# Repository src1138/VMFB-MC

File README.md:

# VMFB-MC
Simplified version of the VMFB (https://github.com/src1138/VMFB) PCB designed with a smaller footprint and BOM to rely on a microcontroller or single-board computer to control and monitor it.

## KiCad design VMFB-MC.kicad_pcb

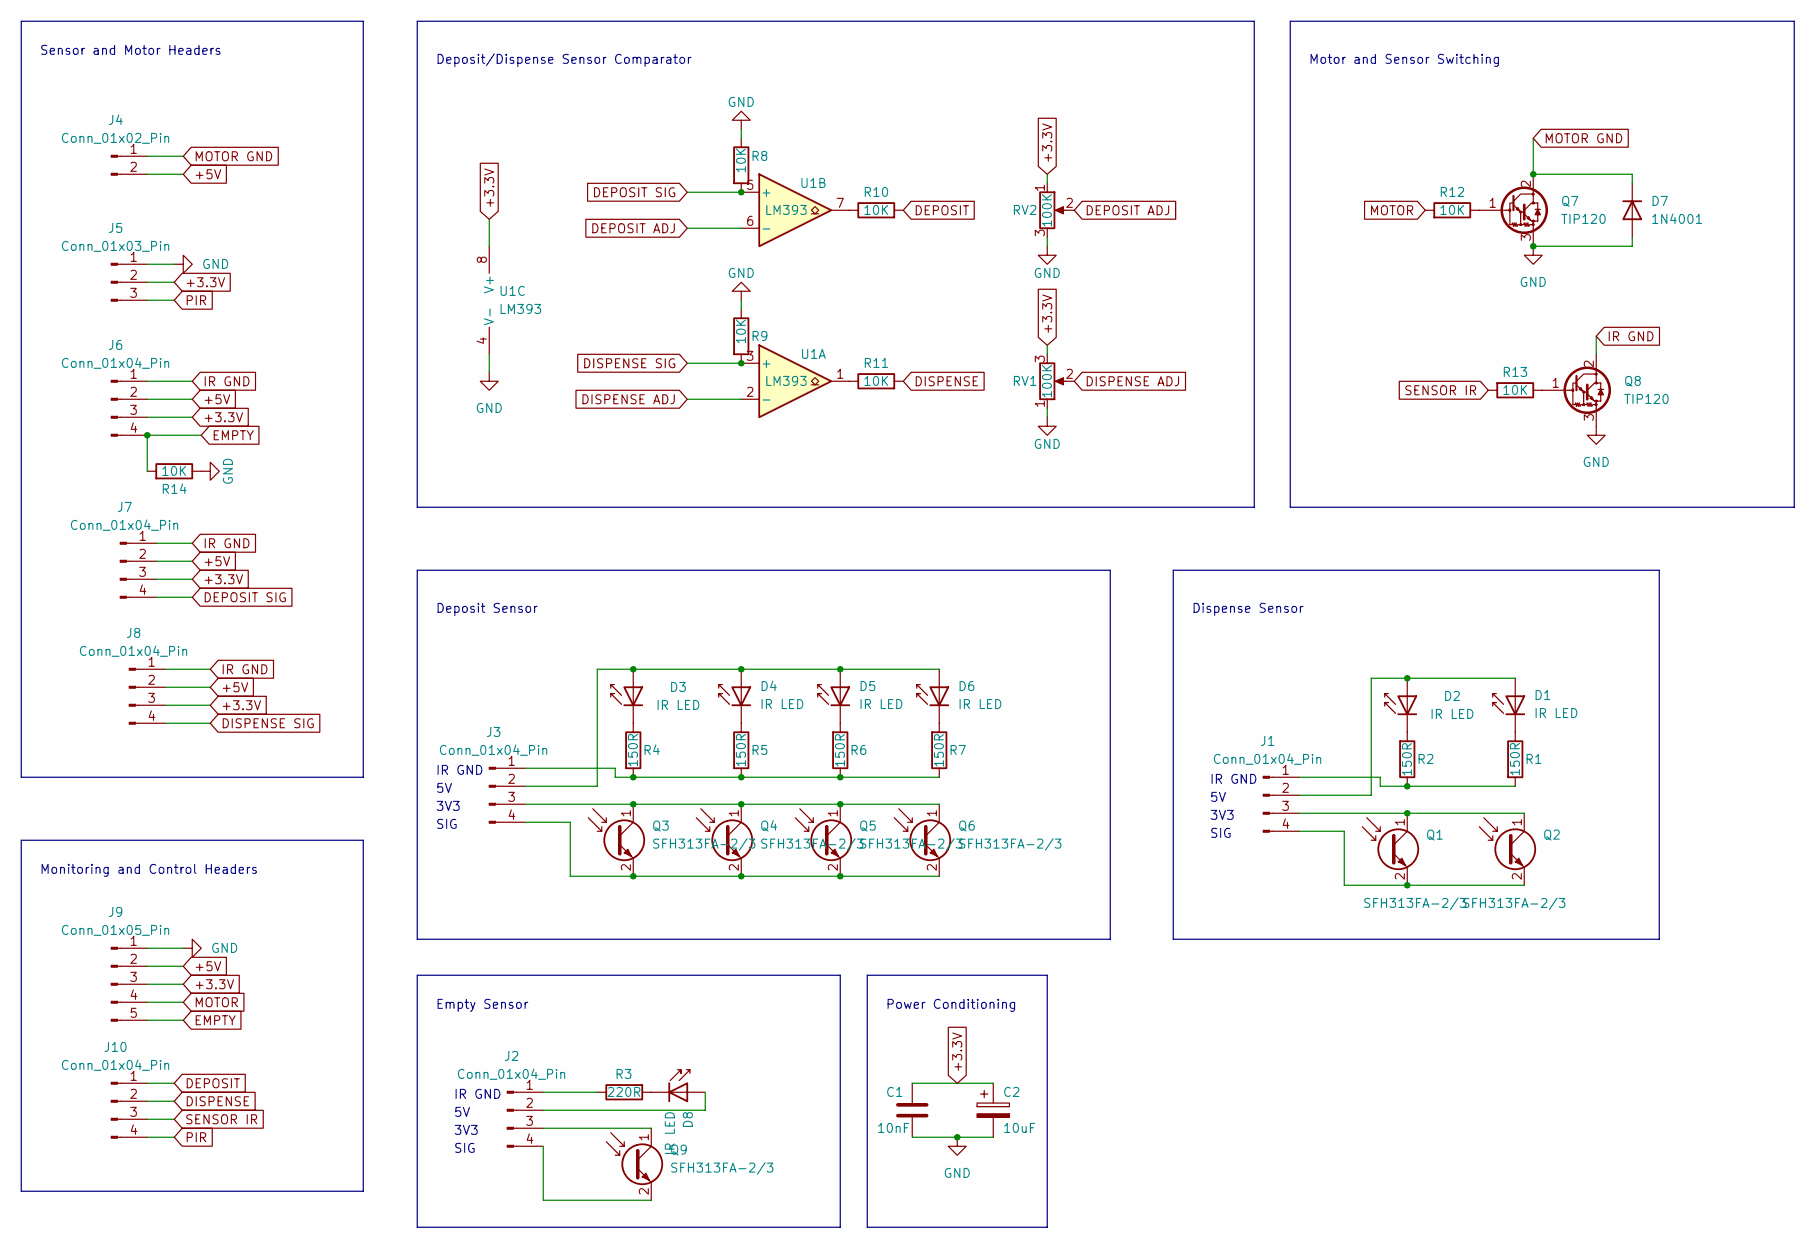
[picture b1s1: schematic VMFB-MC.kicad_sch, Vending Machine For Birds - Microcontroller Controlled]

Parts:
C1: 10nF; C_Disc_D5.0mm_W2.5mm_P2.50mm
C2: 10uF; CP_Radial_D5.0mm_P2.00mm
D1, D2, D3, D4, D5, D6, D8: IR LED; LED_D5.0mm_IRGrey
D7: 1N4001; D_DO-41_SOD81_P2.54mm_Vertical_KathodeUp
J1, J2, J3, J6, J7, J8, J10: Conn_01x04_Pin; PinHeader_1x04_P2.54mm_Vertical
J4: Conn_01x02_Pin; PinHeader_1x02_P2.54mm_Vertical
J5: Conn_01x03_Pin; PinHeader_1x03_P2.54mm_Vertical
J9: Conn_01x05_Pin; PinHeader_1x05_P2.54mm_Vertical
Q1, Q2, Q3, Q4, Q5, Q6, Q9: SFH313FA-2/3; LED_D5.0mm_IRBlack
Q7, Q8: TIP120; TO-220-3_Vertical
R1, R2, R4, R5, R6, R7: 150R; R_Axial_DIN0207_L6.3mm_D2.5mm_P2.54mm_Vertical
R3: 220R; R_Axial_DIN0207_L6.3mm_D2.5mm_P2.54mm_Vertical
R8, R9, R10, R11, R12, R13, R14: 10K; R_Axial_DIN0207_L6.3mm_D2.5mm_P2.54mm_Vertical
RV1, RV2: 100K; Potentiometer_Piher_PT-10-V10_Vertical
U1: LM393; DIP-8_W7.62mm

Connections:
+3.3V: C1.1, C2.1, J5.2, J6.3, J7.3, J8.3, J9.3, RV1.3, RV2.1, U1.8 (V+)
+5V: J4.2, J6.2, J7.2, J8.2, J9.2
DEPOSIT: J10.1, R10.2
DEPOSIT ADJ: RV2.2, U1.6 (-)
DEPOSIT SIG: J7.4, R8.2, U1.5 (+)
DISPENSE: J10.2, R11.2
DISPENSE ADJ: RV1.2, U1.2 (-)
DISPENSE SIG: J8.4, R9.2, U1.3 (+)
EMPTY: J6.4, J9.5, R14.2
GND: C1.2, C2.2, D7.2 (A), J5.1, J9.1, Q7.3 (E), Q8.3 (E), R8.1, R9.1, R14.1, RV1.1, RV2.3, U1.4 (V-)
IR GND: J6.1, J7.1, J8.1, Q8.2 (C)
MOTOR: J9.4, R12.2
MOTOR GND: D7.1 (K), J4.1, Q7.2 (C)
unnamed: D1.2 (A), D2.2 (A), J1.2
unnamed: D1.1 (K), R1.1
unnamed: D2.1 (K), R2.2
unnamed: D3.2 (A), D4.2 (A), D5.2 (A), D6.2 (A), J3.2
unnamed: D3.1 (K), R4.1
unnamed: D4.1 (K), R5.1
unnamed: D5.1 (K), R6.2
unnamed: D6.1 (K), R7.2
unnamed: D8.2 (A), J2.2
unnamed: D8.1 (K), R3.2
unnamed: J1.1, R1.2, R2.1
unnamed: J1.3, Q1.1 (C), Q2.1 (C)
unnamed: J1.4, Q1.2 (E), Q2.2 (E)
unnamed: J2.1, R3.1
unnamed: J2.3, Q9.1 (C)
unnamed: J2.4, Q9.2 (E)
unnamed: J3.1, R4.2, R5.2, R6.1, R7.1
unnamed: J3.3, Q3.1 (C), Q4.1 (C), Q5.1 (C), Q6.1 (C)
unnamed: J3.4, Q3.2 (E), Q4.2 (E), Q5.2 (E), Q6.2 (E)
unnamed: Q7.1 (B), R12.1
unnamed: Q8.1 (B), R13.1
unnamed: R10.1, U1.7
unnamed: R11.1, U1.1
PIR: J5.3, J10.4
SENSOR IR: J10.3, R13.2

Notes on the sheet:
Sensor and Motor Headers
IR GND
Monitoring and Control Headers
3V3
Motor and Sensor Switching
SIG
Deposit Sensor
Dispense Sensor
Empty Sensor
Power Conditioning
Deposit/Dispense Sensor Comparator

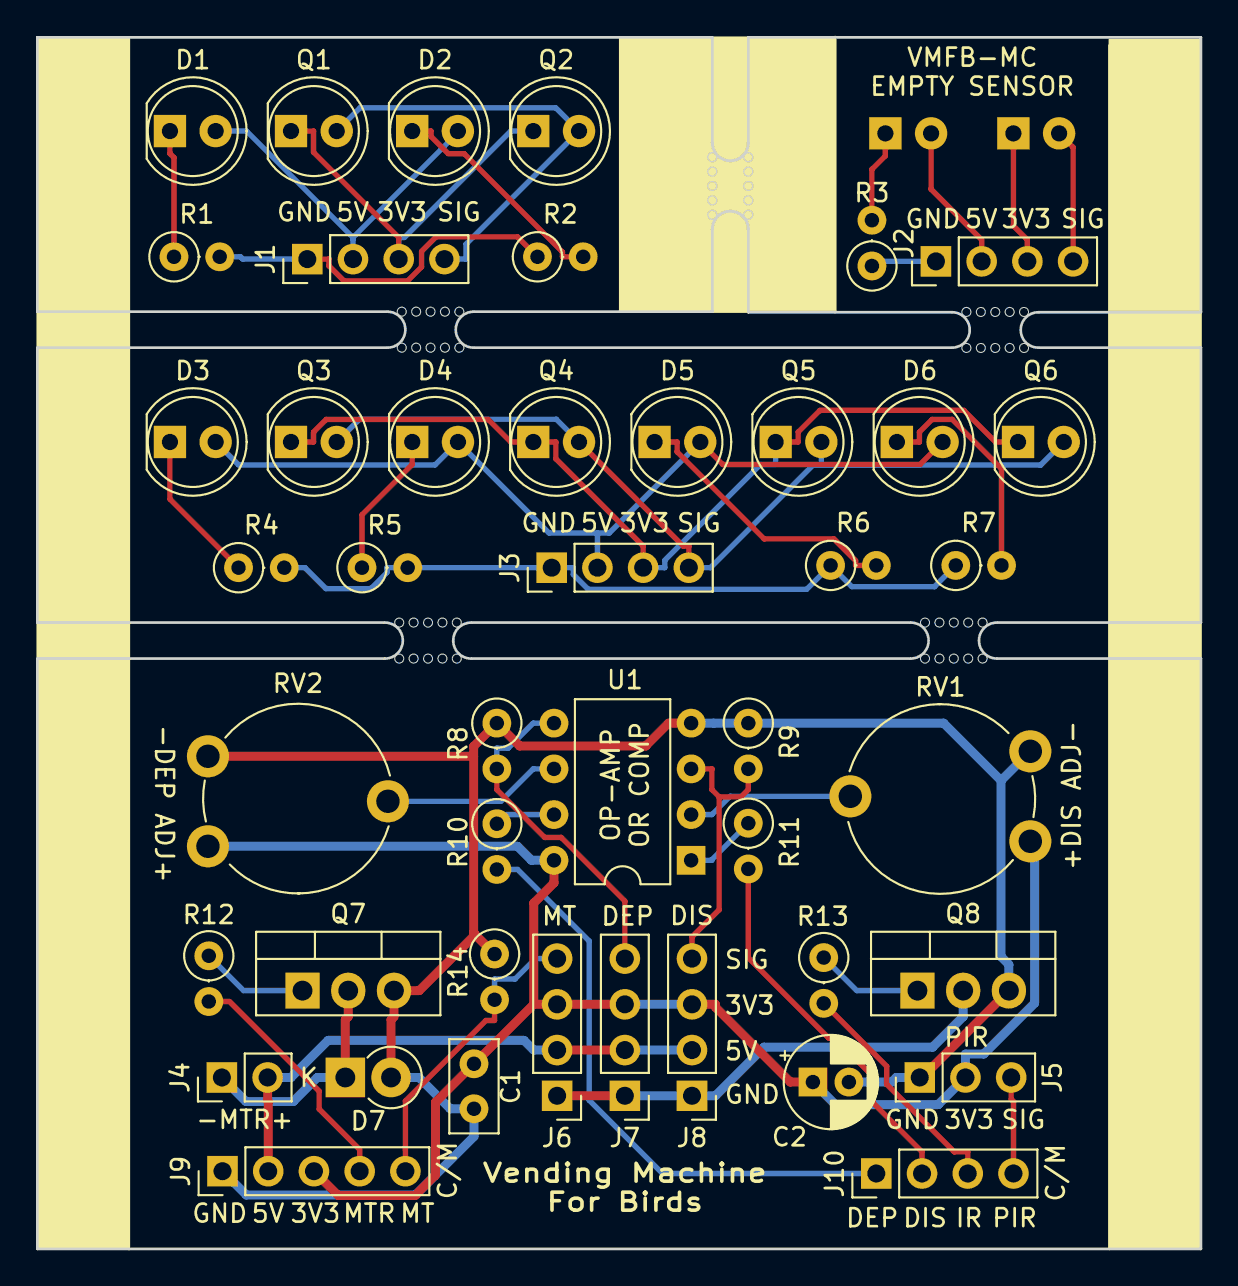
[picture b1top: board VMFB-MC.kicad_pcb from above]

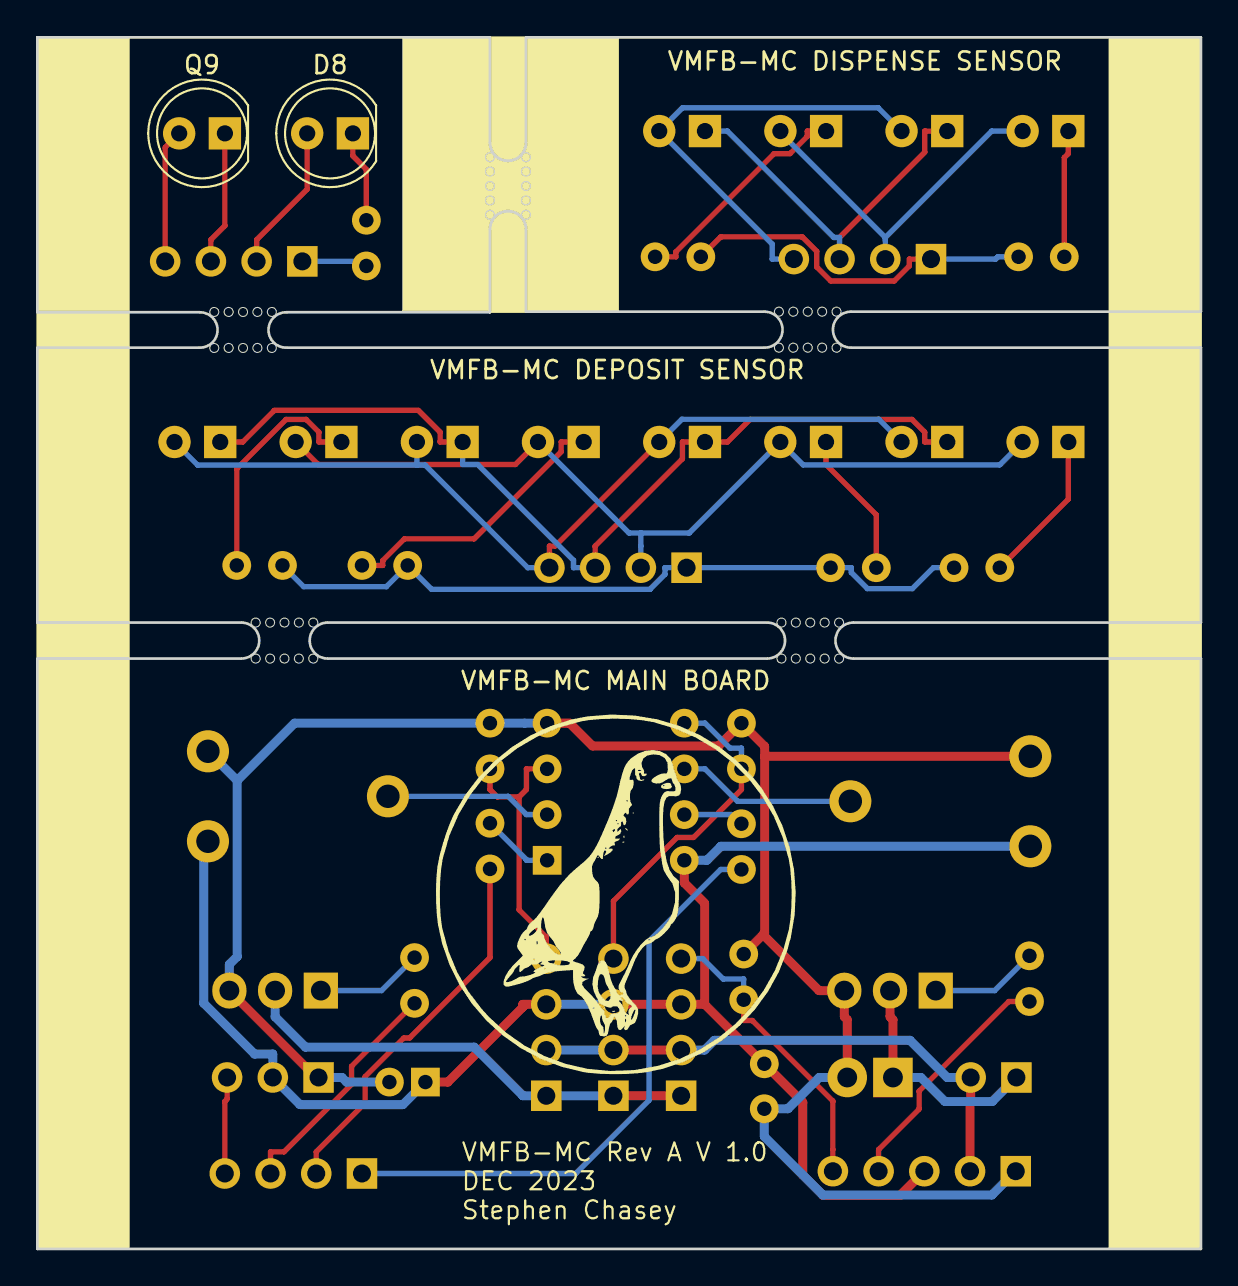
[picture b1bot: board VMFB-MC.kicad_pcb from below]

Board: 2 copper layers, 64.6 x 67.3 mm, 46 parts (2 on the bottom side), 38 nets.

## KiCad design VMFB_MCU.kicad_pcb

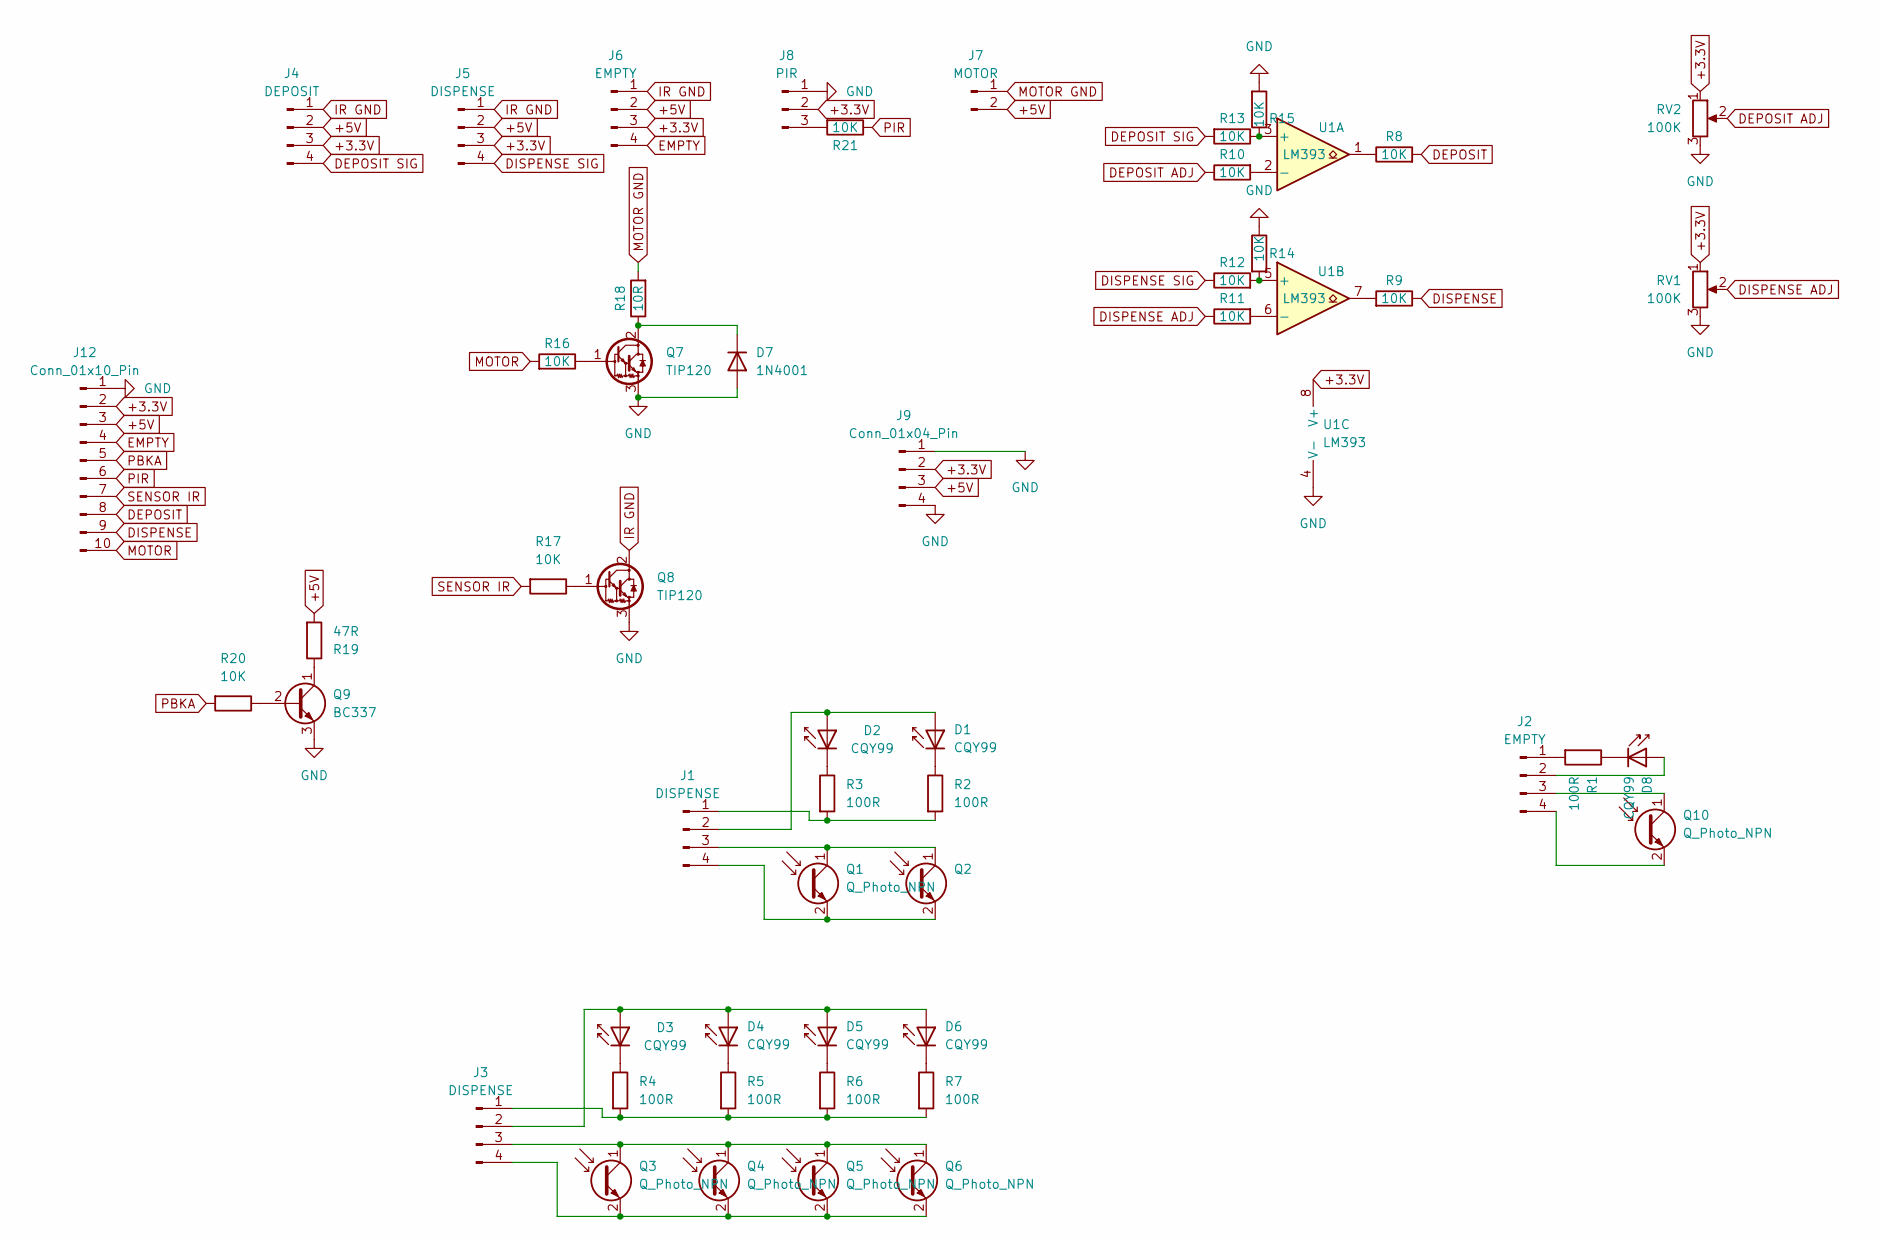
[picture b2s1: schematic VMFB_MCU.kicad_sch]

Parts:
D1, D2, D3, D4, D5, D6, D8: CQY99; LED_D5.0mm_IRGrey
D7: 1N4001; D_DO-41_SOD81_P2.54mm_Vertical_KathodeUp
J1, J3, J5: DISPENSE; PinHeader_1x04_P2.54mm_Vertical
J2, J6: EMPTY; PinHeader_1x04_P2.54mm_Vertical
J4: DEPOSIT; PinHeader_1x04_P2.54mm_Vertical
J7: MOTOR; PinHeader_1x02_P2.54mm_Vertical
J8: PIR; PinHeader_1x03_P2.54mm_Vertical
J9: Conn_01x04_Pin; PinHeader_1x04_P2.54mm_Vertical
J12: Conn_01x10_Pin; PinHeader_1x10_P2.54mm_Vertical
Q1, Q2, Q3, Q4, Q5, Q6, Q10: Q_Photo_NPN; LED_D5.0mm_IRBlack
Q7, Q8: TIP120; TO-220-3_Vertical
Q9: BC337; TO-92_Inline_Wide
R1, R2, R3, R4, R5, R6, R7: 100R; R_Axial_DIN0207_L6.3mm_D2.5mm_P2.54mm_Vertical
R8, R9, R10, R11, R12, R13, R14, R15, R16, R17, R20, R21: 10K; R_Axial_DIN0207_L6.3mm_D2.5mm_P2.54mm_Vertical
R18: 10R; R_Axial_DIN0414_L11.9mm_D4.5mm_P5.08mm_Vertical
R19: 47R; R_Axial_DIN0309_L9.0mm_D3.2mm_P2.54mm_Vertical
RV1, RV2: 100K; Potentiometer_Piher_PT-15-V02_Vertical
U1: LM393; DIP-8_W7.62mm

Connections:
+3.3V: J4.3, J5.3, J6.3, J8.2, J9.2, J12.2, RV1.1, RV2.1, U1.8 (V+)
+5V: J4.2, J5.2, J6.2, J7.2, J9.3, J12.3, R19.2
DEPOSIT: J12.8, R8.2
DEPOSIT ADJ: R10.1, RV2.2
DEPOSIT SIG: J4.4, R13.2
DISPENSE: J12.9, R9.1
DISPENSE ADJ: R11.1, RV1.2
DISPENSE SIG: J5.4, R12.1
EMPTY: J6.4, J12.4
GND: D7.2 (A), J8.1, J9.1, J9.4, J12.1, Q7.3 (E), Q8.3 (E), Q9.3 (E), R14.1, R15.2, RV1.3, RV2.3, U1.4 (V-)
IR GND: J4.1, J5.1, J6.1, Q8.2 (C)
MOTOR: J12.10, R16.2
MOTOR GND: J7.1, R18.2
unnamed: D1.2 (A), D2.2 (A), J1.2
unnamed: D1.1 (K), R2.1
unnamed: D2.1 (K), R3.1
unnamed: D3.2 (A), D4.2 (A), D5.2 (A), D6.2 (A), J3.2
unnamed: D3.1 (K), R4.1
unnamed: D4.1 (K), R5.1
unnamed: D5.1 (K), R6.1
unnamed: D6.1 (K), R7.1
unnamed: D7.1 (K), Q7.2 (C), R18.1
unnamed: D8.2 (A), J2.2
unnamed: D8.1 (K), R1.1
unnamed: J1.1, R2.2, R3.2
unnamed: J1.3, Q1.1 (C), Q2.1 (C)
unnamed: J1.4, Q1.2 (E), Q2.2 (E)
unnamed: J2.1, R1.2
unnamed: J2.3, Q10.1 (C)
unnamed: J2.4, Q10.2 (E)
unnamed: J3.1, R4.2, R5.2, R6.2, R7.2
unnamed: J3.3, Q3.1 (C), Q4.1 (C), Q5.1 (C), Q6.1 (C)
unnamed: J3.4, Q3.2 (E), Q4.2 (E), Q5.2 (E), Q6.2 (E)
unnamed: J8.3, R21.2
unnamed: Q7.1 (B), R16.1
unnamed: Q8.1 (B), R17.1
unnamed: Q9.2 (B), R20.1
unnamed: Q9.1 (C), R19.1
unnamed: R8.1, U1.1
unnamed: R9.2, U1.7
unnamed: R13.1, R15.1, U1.3 (+)
unnamed: R10.2, U1.2 (-)
unnamed: R12.2, R14.2, U1.5 (+)
unnamed: R11.2, U1.6 (-)
PBKA: J12.5, R20.2
PIR: J12.6, R21.1
SENSOR IR: J12.7, R17.2

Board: 2 copper layers, 52 parts (2 on the bottom side), 47 nets, no tracks yet.

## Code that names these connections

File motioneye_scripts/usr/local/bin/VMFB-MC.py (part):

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from gpiozero import LED # for GPIO access

# Configuration variables
SENSOR_IR_TIMEOUT=30		# seconds the sensors stay on after last PIR trigger
MOTOR_TIMEOUT=10		# soconds dispenser motor stays on before it times out
TIMED_DISPENSE_PERIOD=3600	# seconds between timed dispense when it is enabled
TIMED_DISPENSE_START_TIME=600	# time of day timed dispense will start when enabled
				# (HHMM format, don't use leading zeros)
TIMED_DISPENSE_END_TIME=1800	# time of day timed dispense will stop when enabled
				# (HHMM format, don't use leading zeros)
PBKA_ON_PERIOD=1		# seconds the PBKA will sink current to keep a powerbank on
PBKA_OFF_PERIOD=10		# seconds between PBKA current sinks
DEFAULT_TOGGLE_TIMED_DISPENSE=1 # set to 1 to enable timer on startup
DEFAULT_TOGGLE_PBKA=0      	# set to 1 to enable PBKA on startup

# Email alert variables
#SMTP_SERVER="<SMTP server address>"	# SMTP server URL
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#SMTP_RECEIVER="<email receiver address>"	# SMTP receiver address

# Set GPIO pin numbers
PIR_PIN=27 		#PIN 13 - input to sense PIR signal
MT_PIN=17 		#PIN 11	- input to sense hopper empty signal
MAN_PIN=26 		#PIN 37 - input to sense manual dispense event
PBKA_PIN=19 	#PIN 35 - input to sense if PBKA is enabled
TMR_PIN=6 		#PIN 31 - input to sense if timer is enabled
CAL_PIN=22      #PIN 15 - input to sense if calibration mode is enabled
DIS_PIN=15 		#PIN 10 - input to sense a deposit event
DEP_PIN=14 		#PIN 8 - input to sense a dispense event
SIR_PIN=18 		#PIN 12 - output to turn on IR sensor LEDs
MTR_PIN=4 		#PIN 7 - output to turn on dispense motor
MT_SIG_PIN=24	#PIN 18 - output to indicate if hopper is (almost) empty
TMR_SIG_PIN=12  #PIN 32 - output to indicate if timed dispense is enabled
PBKA_SIG_PIN=16 #PIN 36 - output to indicate if PBKA is enabled
CAL_SIG_PIN=23  #PIN 16 - output to indicate if calibration mode is enabled
MAN_SIG_PIN=20  #PIN 38 - output to trigger manual dispense

# Configure GPIO inputs with pull-downs
PIR = Button(PIR_PIN, pull_up=False, bounce_time=1)
MT = Button(MT_PIN, pull_up=False, bounce_time=1)
MAN = Button(MAN_PIN, pull_up=False, bounce_time=0.5)
PBKA = Button(PBKA_PIN, pull_up=False, bounce_time=0.2)
TMR = Button(TMR_PIN, pull_up=False, bounce_time=0.2)
CAL = Button(CAL_PIN, pull_up=False, bounce_time=0.2)

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def pir_event(pin=None):
    '''Turns the sensor IR LEDs on'''
    #print("Start pir_event()")
    log_event("PIR",1,pin)
    # Turn on the sensors if not in calibration mode
    sensor_ir_on(pin)
    #print("End pir_event()")

# When sensors are on, checks the empty sensor and updates the MT_SIG pin state
# Takes this approach because when the sensor LEDs are off the signal is always low
def update_mt(pin=None):
    '''Updates the value of the empty indicator output pin'''
    #print("Start update_mt()")
    event=0
    if MT.value == 1:
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
# Suspends PBKA if it is enabled, turns on sensor LEDs,
# updates empty sensor status, and (re)starts sensor timeout timer
def sensor_ir_on(pin=PIR_PIN):
    '''Turns the IR LEDs for the sensors on'''
    #print("Start sensor_ir_on()")
    log_event("SIR","ON",pin)
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    DIS.when_released = dispense_event
    # if the trigger came from the PIR, enable camera, enable motion detection in motioneye
    # and log the event
    if pin == PIR_PIN:
        # enable the camera
        # enable_camera(pin)
        # enable motion detection
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def manual_dispense(pin=None):
    '''Dispenses a peanut''' 
    #print("Start manual_dispense()")
    log_event("MAN","DISPENSE",pin)
    sensor_ir_on(pin)
    motor_on(pin)
    #print("End manual_dispense()")
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    # of operation on certain days or dates you can do so in
    # the following if statement
    if (now_time >= TIMED_DISPENSE_START_TIME) & (now_time <= TIMED_DISPENSE_END_TIME):
        log_event("TMR","DISPENSE",pin)
        sensor_ir_on(pin)
        motor_on(pin)
    else:
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    log_event("TMR","SUSPEND",pin)
    #print("End suspend_timed_dispense()")

# When the TMR pin changes state, (re)starts the timed dispense
# timer if it is high, stops it when it is low
def toggle_timed_dispense(pin=None):
    '''Check the TMR gpio pin value and enable(1) or disable(0) timed dispense''' 
    #print("Start toggle_timed_dispense()")
    event="DISABLED"
    global timed_dispense_timer
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        global pbka_idle_timer
        if pbka_idle_timer.is_alive() is True:
            pbka_idle_timer.cancel()
    log_event("PBKA","SUSPEND",pin)
    #print("End suspend_pbka()")

# When the PBKA pin changes state or sensors turn off when the PBKA is enabled,
# (re)starts the PBKA Off timer to start the current sink cycle
# When PBKA is disabled, it stops the PBKA timers
def toggle_pbka(pin=None):
    '''Check the PBKA gpio pin value and enable(1) or disable(0) current sinking''' 
    #print("Start toggle_pbka()")
    event="DISABLED"
    if PBKA.value == 1:
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            pbka_sink_timer.cancel()
        if pbka_idle_timer.is_alive() is True:
            pbka_idle_timer.cancel()
    log_event("PBKA",event,pin)
    #print("End toggle_pbka()")

# Turns on sensor LEDs to sink current and keep powerbanks on,
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def pbka_sink(pin="TO"):
    '''Starts timer to trigger the end of the sink'''
    #print("Start pbka_sink()")
    log_event("PBKA","SINK",pin)
    SIR.on()
    global pbka_sink_timer
    if pbka_sink_timer.is_alive() is True:
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def pbka_idle(pin="TO"):
    '''Starts timer to trigger the next sink'''
    #print("Start pbka_idle()")
    log_event("PBKA","IDLE",pin)
    SIR.off()
    global pbka_idle_timer
    if pbka_idle_timer.is_alive() is True:
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
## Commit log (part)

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2023-11-21 Initial commit
    Basic circuit complete and layout in progress.
2023-11-21 Delete fp-info-cache
    Renaming...
2023-11-21 Delete VMFB_MCU.kicad_sch
    Renaming...
2023-11-21 Delete VMFB_MCU.kicad_pro
    Renaming...
2023-11-21 Delete VMFB_MCU.kicad_prl
    Renaming...
2023-11-21 Delete VMFB_MCU.kicad_pcb
    Renaming...
2023-11-21 Renamed files to match repo
2023-12-05 New layour and routing
2023-12-05 synching stuff
2023-12-05 Update README.md
    Slightly updated readme
2023-12-07 updating netclasses, adding routing
2023-12-07 cleaned up tracks
2023-12-11 layout update
    updates layout to compress it a bit.
2023-12-11 Layout tweaks
    more layout and labelling tweaks
2023-12-12 silkscreen and label tweaks
2023-12-12 updated title
2023-12-12 cleanup schematic
2023-12-12 cleanup netclasses
2023-12-12 minor tweaks
2023-12-13 removed 10R motor resistor and extra power header, revised placement
2023-12-13 reannotated
2023-12-13 more placement tweaks
2023-12-18 removed power bank keep alive - can just turn on the sensors to sink curent if needed, revised layout to accomodate this
2023-12-18 added routes
2023-12-18 reduced footprint
    footprint is now 65x68mm
2023-12-24 MT bleeder resistor
    Added bleeder resistor to the MT sensor.
2023-12-24 Cleaned up tracks placement on MT sensor
2023-12-24 Cleaned up BOM naming
2023-12-25 clean up
    removed some unnecessary components and revised component placement.
2023-12-25 adding xml and sym files
2023-12-25 net clean up
2023-12-25 more clean up
2023-12-25 removed stray silkscreen label
2023-12-26 more cleanup
2023-12-26 even more cleanup
2023-12-26 better schematic labelling
2023-12-27 schematic labelling
2024-01-02 adding stubs for motioneye scripts
2024-01-07 a little more progress on motioneye scripts - still not ready
2024-01-19 Action buttons and Timer tweaks
2024-01-20 more tweaks
2024-01-21 More tweaks and corrections
2024-01-21 added PBKA script
2024-01-21 added/fixed some comments
2024-01-21 more comments
2024-01-22 More comment corrections
2024-01-22 Comment and pin assignment corrections
2024-01-22 More pin assignment corrections and pinout image
2024-01-22 more pin assignment comments/corrections
2024-01-22 more pin comments/corrections
2024-01-23 debugging
2024-01-24 More debugging
2024-01-24 Removing PBKA buttons
    This is not something you will be turning on and off often.
2024-01-24 update overlay text
2024-02-06 refactored and consolidated most logic to python
2024-02-06 cleanup
2024-02-07 formatting fixes
2024-02-08 cleanup, exporting all GPIOs
2024-02-16 debugging and optimization
2024-02-18 more code comments
2024-02-18 better event logging - still needs work
2024-02-18 fixd grep counter
2024-02-18 More logging and comment tweaks
2024-02-18 logging and monitoring fixes
2024-02-19 bug fixes - still more work to do
2024-02-19 debugging - should be ready soon
2024-02-20 tweaks and debugging
2024-02-21 added comment about interrupt bouncetime
2024-02-23 Fixed initial false positives on dispense sensor
    Moved adding DEP and DIS interrupts to the end of the sensorsOn routine and remove them in sensorsOff.
    This way, sensors can only trigger when the IR LEDs are on, and the short delay in enabling the interrupts avoids the initial blip you can get from phototransistors.
2024-02-23 Manual dispense debug and improved overlay info
2024-02-25 enable and disable mtion detection on PIR trigger/timeout
2024-02-26 debugging motion detect control calls
2024-02-26 debugging empty notification
2024-02-26 more debugging and adding motion event in logs
2024-02-28 tweak monitor overlay
2024-02-28 tweaking overlay
2024-02-29 more overlay tweaks
2024-02-29 Update monitor_1
2024-03-17 Added functions to enable/disable camera to save power
    Optional calls to enable camera when the sensors are on and disable it when sensors are off. This can save power as camera modules typically take 100-300mA to run.
    When using an RPi Zero W with HDMI disabled, this brings idle current comsumption to about 75mA.
2024-03-22 debug
    non-ASCII quotes...
2024-03-27 Adding configurable startup state for PBKA and timed dispense.
2024-03-28 Fixed windows newline, updated comment
2024-03-28 Initialize the MT Sensor on startup
2024-03-29 add sleep to allow VMFB-MC.py time to set up interrupts before initializing PBKA and Timer
2024-03-29 Adding sleep to give VMFB-MC.py a chance to set up interrupts and timers before executing
2024-03-31 removed merge artifact and set timer to dispense every 60min
2024-03-31 again removing merge artifacts and setting timed dispense to 1 hour
2024-04-02 Moved PBKA and Timer init into VMFB-MC.py
2024-04-02 Moved PBKA and timed dispense init to VMFB-MC.py
2024-04-02 fix var name typo
2024-04-02 stringify the init values to concatenate with strings
2024-04-02 changed Empty Sensor LED resistor from 1K to 220R
2024-04-03 added code to handle PIRs that stay triggered
2024-04-03 change deposit/dispense trigger edge to falling
2024-04-03 Increasing sleep
2024-04-03 increase sleep with comment
2024-04-04 optimize camera disable/enable
2024-04-04 optimize deposit/dispense interrupts
2024-04-10 fixed indentation issue causing segfault
2024-04-10 logging cleanup
2024-04-21 Add conditional to handle dispense sensor jams
    If the dispense sensor is triggering when a deposit is sensed, it will assume there is a jam and the motor won't be turned on.
2024-04-21 Added comments about deposit/dispense interrupts
2024-04-23 updates - encountering some segfaults again
2024-04-24 Refactoring code a bit - still having issues with resource usage
2024-04-24 More refactoring
2024-04-24 replaced tab indentation with spaces (4 per level)
2024-04-24 whitespace cleanup
2024-04-24 more pylint cleanup
2024-04-24 pylint cleanup
2024-04-24 cleanup thread status checking statements
2024-04-24 cleaned up file handling in camera enable/disable
2024-04-24 fix bad syntax on file handling
2024-04-25 reference PIR pin value by variable instead of literal
2024-04-26 script is hanging, comment cleanup
2024-04-26 removed global decs in functions for timers
2024-04-26 restored global decs, removed trailing whitespace on comments
2024-04-29 added debugging print statements, fixed some comments - appears to be working again
2024-05-20 Adding calibration mode
2024-05-21 Change pin assignments
2024-05-21 fix indentation
2024-05-21 remove trailing whitespace
2024-05-22 Updating RPi pimout diagram
2024-05-22 add legend for pinout
2024-05-22 finish gpio pin reassignment
2024-05-22 fix calibration script name
2024-05-22 fix typo in calibration action button script
2024-05-22 add CAL pins to gpio init
2024-05-23 turn off motor when entering calibration mode
2024-05-23 fix typo in MT pin assignment
2024-05-23 only check PIR status when turning off sensors due to timout
2024-05-23 debugging calibration mode - PIR and sensors are not registered in the interface
2024-05-23 debugging calibration mode
2024-05-23 clean up syntax and naming
2024-05-23 refactoring
2024-05-24 cleanup
    add module docstring and use fromimport instead of import/as for RPi.GPIO
2024-07-24 adding email alerts
2024-07-26 Fixed email thread mistake and moved email logging to end of function
2024-08-14 Added email alerts, clean up
    Added email alerts for dispense timeout and empty/not empty state change.
    Removed commented out urllib2 import since this is no longer being used.
2024-08-14 Add email alert for startup
    will help detect when the system reboots
2024-08-14 declare timers as global in functions
    not declaring as global caused failure to end timer threads before they run out.
2025-01-13 Added caps to the 3.3V rail
2025-01-15 Minor tweak to PCB
2026-03-13 Update README_motioneye.md
    added info on calibration mode button
